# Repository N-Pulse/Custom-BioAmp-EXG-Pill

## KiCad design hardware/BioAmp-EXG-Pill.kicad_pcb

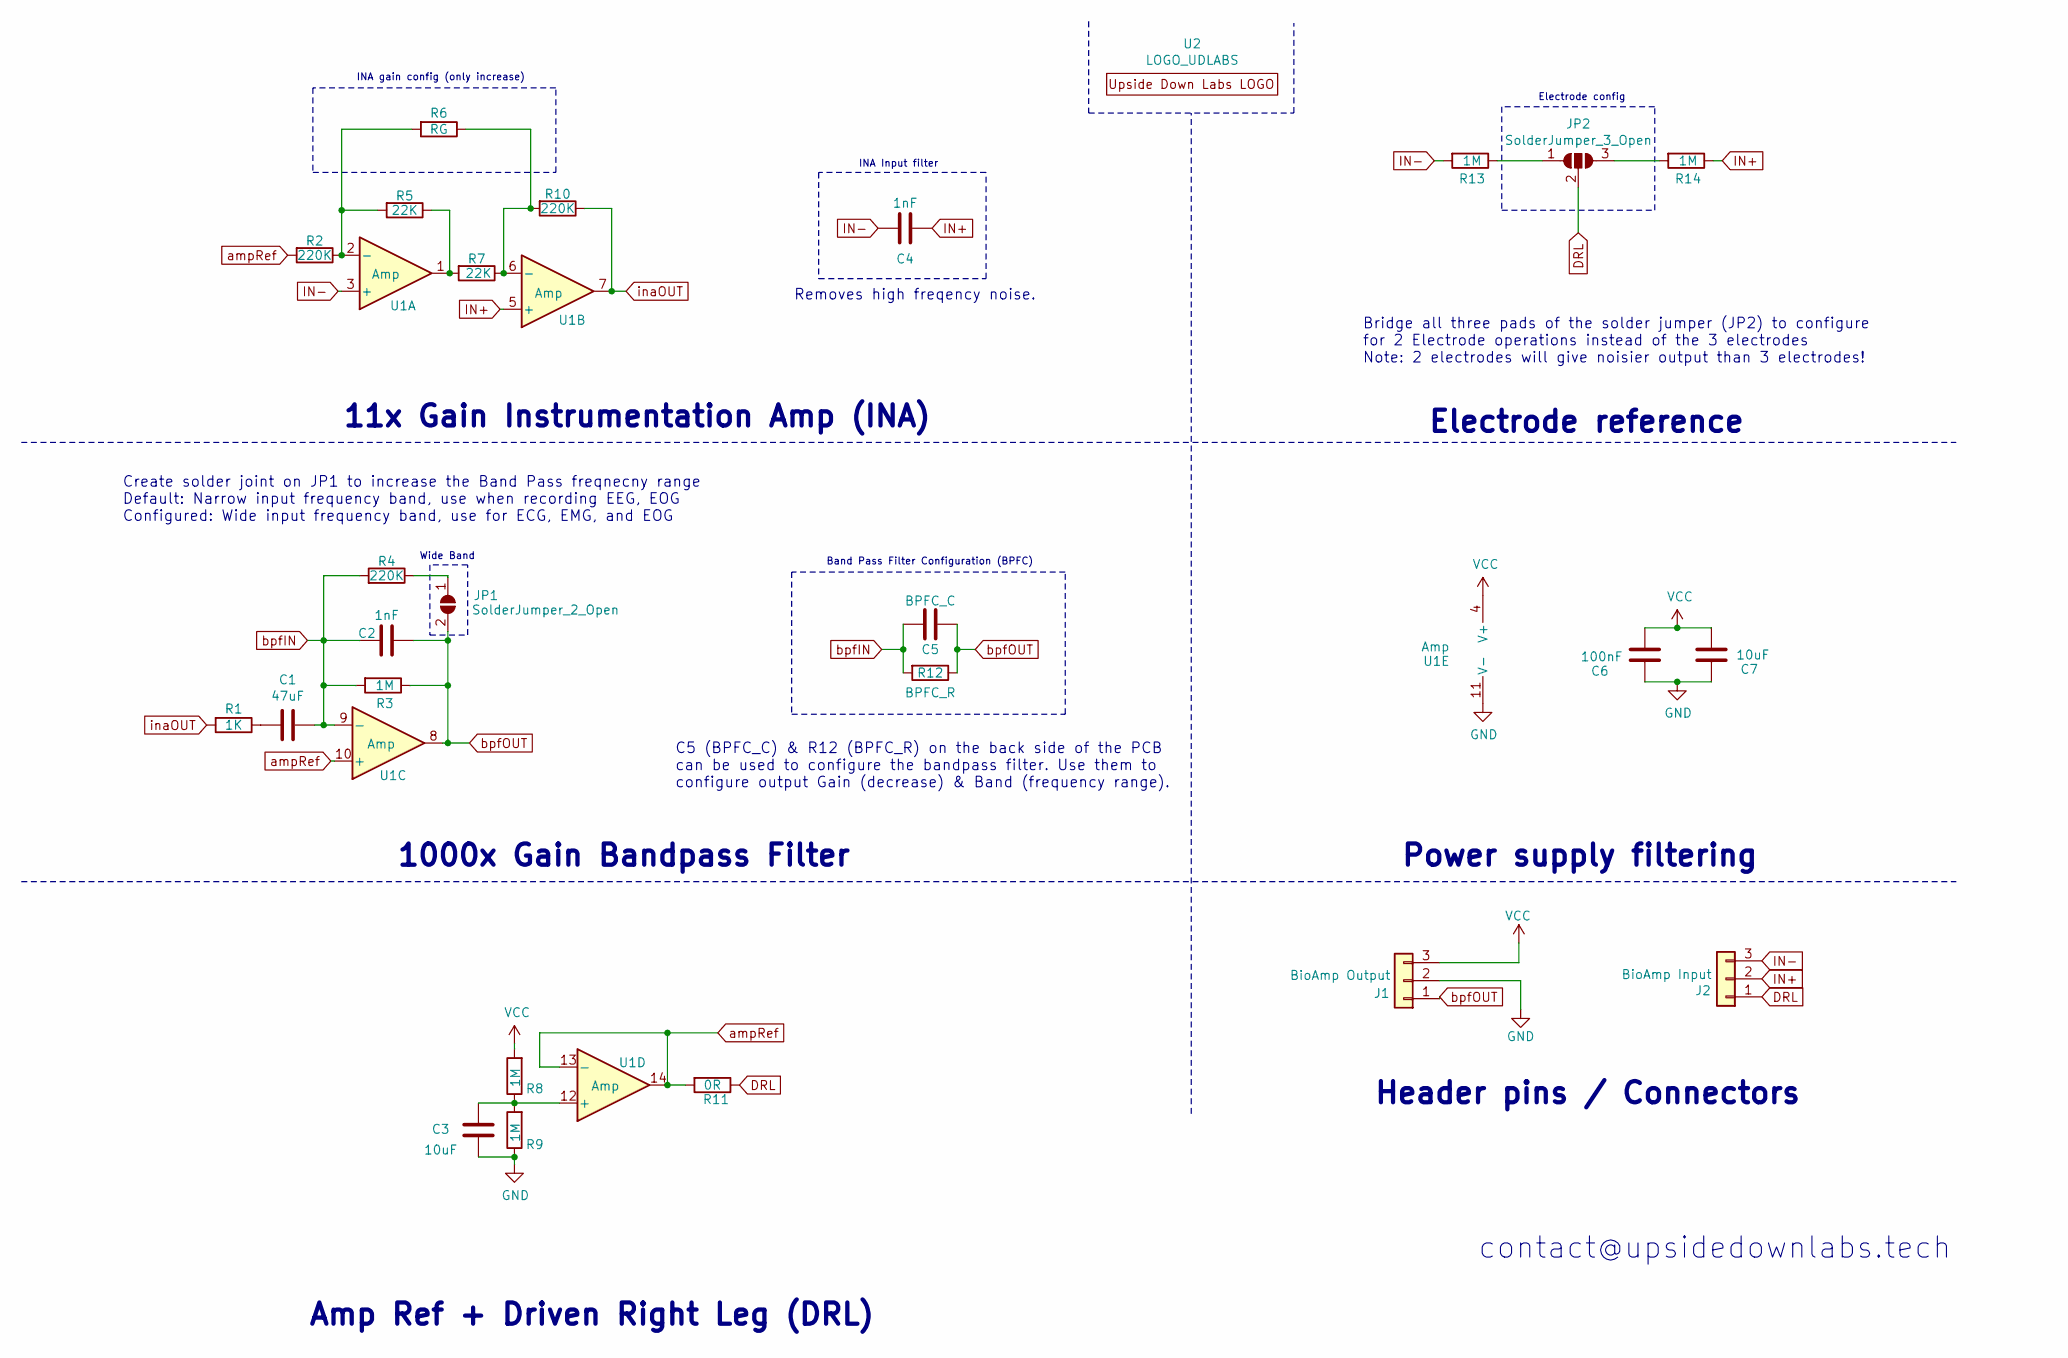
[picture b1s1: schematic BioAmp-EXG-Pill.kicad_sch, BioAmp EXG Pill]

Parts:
C1: 47uF; C_0805_2012Metric_Pad1.18x1.45mm_HandSolder
C2, C4: 1nF; C_0603_1608Metric_Pad1.08x0.95mm_HandSolder
C3, C7: 10uF; C_0603_1608Metric_Pad1.08x0.95mm_HandSolder
C5: BPFC_C; C_0603_1608Metric_Pad1.08x0.95mm_HandSolder
C6: 100nF; C_0603_1608Metric_Pad1.08x0.95mm_HandSolder
J1: BioAmp Output; PinHeader_1x03_P2.54mm_Vertical
J2: BioAmp Input; PinHeader_1x03_P2.54mm_Vertical
JP1: SolderJumper_2_Open; SolderJumper-2_P1.3mm_Open_RoundedPad1.0x1.5mm
JP2: SolderJumper_3_Open; SolderJumper-3_P1.3mm_Open_RoundedPad1.0x1.5mm
R1: 1K; R_0603_1608Metric_Pad0.98x0.95mm_HandSolder
R2, R4, R10: 220K; R_0603_1608Metric_Pad0.98x0.95mm_HandSolder
R3, R8, R9, R13, R14: 1M; R_0603_1608Metric_Pad0.98x0.95mm_HandSolder
R5, R7: 22K; R_0603_1608Metric_Pad0.98x0.95mm_HandSolder
R6: RG; R_0603_1608Metric_Pad0.98x0.95mm_HandSolder
R11: 0R; R_0603_1608Metric_Pad0.98x0.95mm_HandSolder
R12: BPFC_R; R_0603_1608Metric_Pad0.98x0.95mm_HandSolder
U1: Amp; TSSOP-14_4.4x5mm_P0.65mm
U2: LOGO_UDLABS; EXG

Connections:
DRL: J2.1, JP2.2 (C), R11.1; also elsewhere on the board
GND: C3.2, C6.1, C7.1, J1.2, R9.1, U1.11 (V-); also elsewhere on the board
IN+: C4.1, J2.2, R14.1, U1.5 (+); also elsewhere on the board
IN-: C4.2, J2.3, R13.2, U1.3 (+); also elsewhere on the board
unnamed: C1.2, R1.1
unnamed: C3.1, R8.1, R9.2, U1.12 (+)
unnamed: JP1.1 (A), R4.1
unnamed: JP2.1 (A), R13.1
unnamed: JP2.3 (B), R14.2
unnamed: R2.1, R5.2, R6.2, U1.2 (-)
unnamed: R5.1, R7.2, U1.1
unnamed: R6.1, R7.1, R10.2, U1.6 (-)
VCC: C6.2, C7.2, J1.3, R8.2, U1.4 (V+); also elsewhere on the board
ampRef: R2.2, R11.2, U1.10 (+), U1.13 (-), U1.14
bpfIN: C1.1, C2.2, C5.2, R3.2, R4.2, R12.2, U1.9 (-)
bpfOUT: C2.1, C5.1, J1.1, JP1.2 (B), R3.1, R12.1, U1.8; also elsewhere on the board
inaOUT: R1.2, R10.1, U1.7

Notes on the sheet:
contact@upsidedownlabs.tech
1000x Gain Bandpass Filter
Create solder joint on JP1 to increase the Band Pass freqnecny range Default: Narrow input frequency band, use when recording EEG, EOG Configured: Wide input frequency band, use for ECG, EMG, and EOG
Band Pass Filter Configuration (BPFC)
Electrode config
C5 (BPFC_C) & R12 (BPFC_R) on the back side of the PCB can be used to configure the bandpass filter. Use them to configure output Gain (decrease) & Band (frequency range).
Header pins / Connectors
11x Gain Instrumentation Amp (INA)
Bridge all three pads of the solder jumper (JP2) to configure for 2 Electrode operations instead of the 3 electrodes Note: 2 electrodes will give noisier output than 3 electrodes!
Power supply filtering
Amp Ref + Driven Right Leg (DRL)
Removes high freqency noise.
Wide Band
INA gain config (only increase)
Electrode reference
INA Input filter

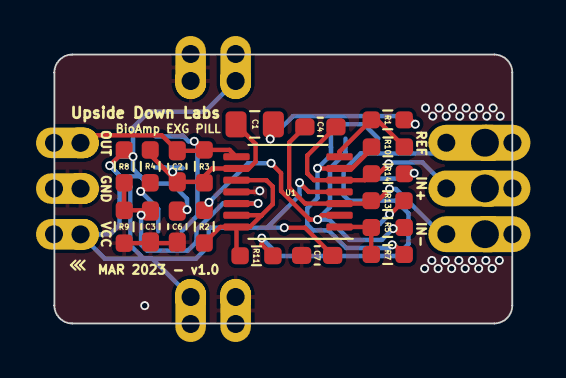
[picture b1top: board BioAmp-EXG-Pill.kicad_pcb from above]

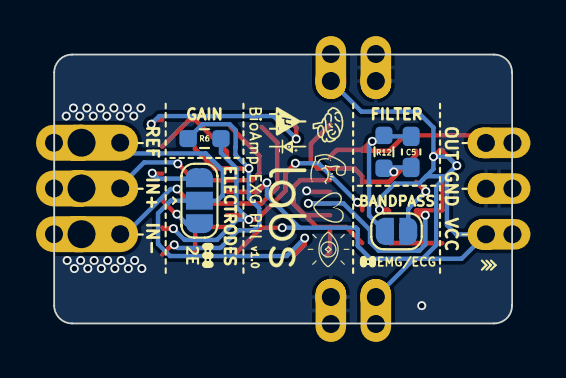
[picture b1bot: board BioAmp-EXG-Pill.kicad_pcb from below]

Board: 2 copper layers, 25.4 x 14.9 mm, 30 parts (6 on the bottom side), 17 nets.

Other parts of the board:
J1#2: BioAmp Output; PinHeader_1x03_P2.54mm_Vertical
J2#2, J2#3: BioAmp Input; PinHeader_1x03_P2.54mm_Vertical

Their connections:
DRL: J2#2.1, J2#3.1; also elsewhere on the board
GND: J1#2.2; also elsewhere on the board
IN+: J2#2.2, J2#3.2; also elsewhere on the board
IN-: J2#2.3, J2#3.3; also elsewhere on the board
VCC: J1#2.3; also elsewhere on the board
bpfOUT: J1#2.1; also elsewhere on the board

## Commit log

2025-03-08 add 2 power connectors for assembly in chain
2025-03-15 add connectors and fill in ground
2025-03-15 shrink the pcb's dimensions
